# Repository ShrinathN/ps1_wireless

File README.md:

# Project to turn any original PS1 or PS2 controller wireless using an AVR and a NRF24L01/NRF24L01+ radio

## Hardware

* atmega8a
* NRF24L01+ / NRF24L01
* PS1 / PS2 controller
* 18650 + TP4056 (I'm using an 18650, but you can choose whatever you want)

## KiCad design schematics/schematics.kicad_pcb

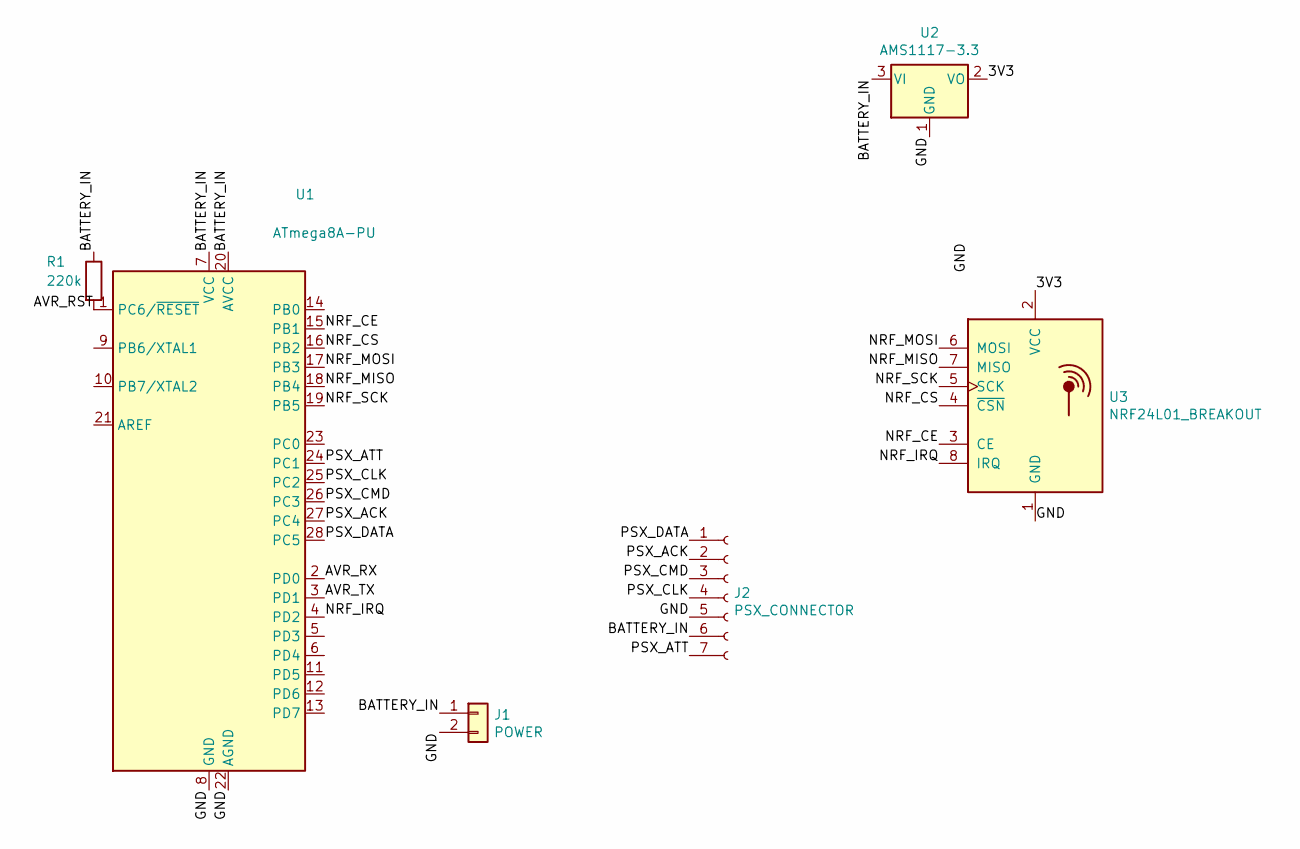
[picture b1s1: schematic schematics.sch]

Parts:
J1: POWER; PinHeader_1x02_P2.00mm_Vertical
J2: PSX_CONNECTOR; PinHeader_1x07_P2.54mm_Vertical
R1: 220k; R_Axial_DIN0204_L3.6mm_D1.6mm_P5.08mm_Horizontal
U1: ATmega8A-PU; DIP-28_W7.62mm
U2: AMS1117-3.3; SOT-223-3_TabPin2
U3: NRF24L01_BREAKOUT; nRF24L01_Breakout

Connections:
/3V3: U2.2 (VO), U3.2 (VCC)
/AVR_RST: R1.2, U1.1 (PC6/~RESET)
/AVR_RX: U1.2 (PD0)
/AVR_TX: U1.3 (PD1)
/BATTERY_IN: J1.1, J2.6, R1.1, U1.7 (VCC), U1.20 (AVCC), U2.3 (VI)
/GND: J1.2, J2.5, U1.8 (GND), U1.22 (AGND), U2.1 (GND), U3.1 (GND)
/NRF_CE: U1.15 (PB1), U3.3 (CE)
/NRF_CS: U1.16 (PB2), U3.4 (~CSN)
/NRF_IRQ: U1.4 (PD2), U3.8 (IRQ)
/NRF_MISO: U1.18 (PB4), U3.7 (MISO)
/NRF_MOSI: U1.17 (PB3), U3.6 (MOSI)
/NRF_SCK: U1.19 (PB5), U3.5 (SCK)
/PSX_ACK: J2.2, U1.27 (PC4)
/PSX_ATT: J2.7, U1.24 (PC1)
/PSX_CLK: J2.4, U1.25 (PC2)
/PSX_CMD: J2.3, U1.26 (PC3)
/PSX_DATA: J2.1, U1.28 (PC5)

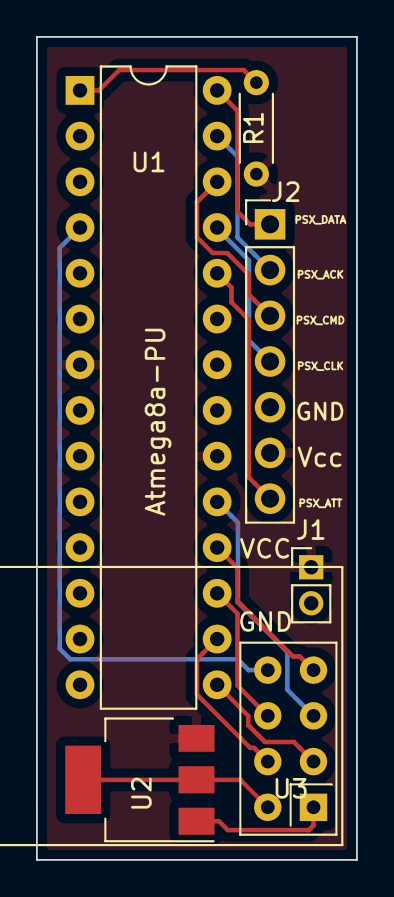
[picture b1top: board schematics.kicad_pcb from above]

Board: 2 copper layers, 17.8 x 45.7 mm, 6 parts (0 on the bottom side), 15 nets.

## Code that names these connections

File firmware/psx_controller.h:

#ifndef PSX_CONTROLLER_H
#define PSX_CONTROLLER_H
#include "main.h"

//constants
#define PSX_DELAY_CLK_US 10
#define PSX_ATT_DELAY_US 20
#define PSX_INTER_BYTE_DELAY_US 20

//pin definitions
#define PSX_ATT_DDR DDRC
#define PSX_ATT_PORT PORTC
#define PSX_ATT_BIT PC1

#define PSX_CLK_DDR DDRC
#define PSX_CLK_PORT PORTC
#define PSX_CLK_BIT PC2

#define PSX_CMD_DDR DDRC
#define PSX_CMD_PORT PORTC
#define PSX_CMD_BIT PC3

#define PSX_ACK_DDR DDRC
#define PSX_ACK_PORT PORTC
#define PSX_ACK_PIN PINC
#define PSX_ACK_BIT PC4

#define PSX_DATA_DDR DDRC
#define PSX_DATA_PORT PORTC
#define PSX_DATA_PIN PINC
#define PSX_DATA_BIT PC5

//MACROS
#define PSX_CLK_LOW PSX_CLK_PORT &= ~(1 << PSX_CLK_BIT)
#define PSX_CLK_HIGH PSX_CLK_PORT |= (1 << PSX_CLK_BIT)
#define PSX_ATT_LOW PSX_ATT_PORT &= ~(1 << PSX_ATT_BIT)
#define PSX_ATT_HIGH PSX_ATT_PORT |= (1 << PSX_ATT_BIT)
#define PSX_CMD_LOW PSX_CMD_PORT &= ~(1 << PSX_CMD_BIT)
#define PSX_CMD_HIGH PSX_CMD_PORT |= (1 << PSX_CMD_BIT)
#define PSX_READ_DATA ((PSX_DATA_PIN & (1 << PSX_DATA_BIT))?(1):(0))
#define PSX_WAIT_ACK while(PSX_ACK_PIN & (1 << PSX_ACK_BIT))
#define PSX_DELAY_US(x) _delay_us(x)

//different types of controllers
enum
{
	PSX_TYPE_DIGITAL = 0x41,
	PSX_TYPE_NEGCON = 0x23,
	PSX_TYPE_ANALOGUE_RED_LED = 0x73,
	PSX_TYPE_ANALOGUE_GREEN_LED = 0x53
};

//function declarations
void PSX_PinsInit();
void PSX_TransRecieveBlock(uint8_t * transmit_block, uint8_t * recieve_block, uint8_t length);

#endif

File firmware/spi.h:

#ifndef SPI_H
#define SPI_H
//header file includes
#include "main.h"

//pin definitions
#define SPI_DIRECTION_REGISTER DDRB
#define SPI_PORT PORTB
#define SPI_SCK_PIN PB5
#define SPI_MISO_PIN PB4
#define SPI_MOSI_PIN PB3
#define SPI_SS_PIN PB2

//macros
#define SPI_WAIT while(!(SPSR & (1 << SPIF))) //for waiting while the SPIF pin is not set in the SPSR register
#define SPI_SS_HIGH SPI_PORT |= (1 << SPI_SS_PIN)
#define SPI_SS_LOW SPI_PORT &= ~(1 << SPI_SS_PIN)

//function declarations
void SPI_Init();
void SPI_Transmit(uint8_t * data, uint8_t length);
void SPI_Receive(uint8_t * buffer, uint8_t length);
void SPI_TransReceive(uint8_t * data, uint8_t * buffer, uint8_t length);

#endif

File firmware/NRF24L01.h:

#ifndef NRF24L01_H
#define NRF24L01_H

#include "main.h"

//pin definitions
//CE pin
#define NRF_CE_DDR DDRB
#define NRF_CE_PORT PORTB
#define NRF_CE_BIT PB1
//IRQ pin
#define NRF_IRQ_DDR DDRD
#define NRF_IRQ_PORT PORTD
#define NRF_IRQ_PIN PIND
#define NRF_IRQ_BIT PD2

//macros
#define NRF_CSN_HIGH SPI_SS_HIGH
#define NRF_CSN_LOW SPI_SS_LOW
#define NRF_CE_HIGH NRF_CE_PORT |= (1 << NRF_CE_BIT)
#define NRF_CE_LOW NRF_CE_PORT &= ~(1 << NRF_CE_BIT)
#define NRF_IRQ_WAIT while((NRF_IRQ_PIN & (1 << NRF_IRQ_BIT)) != 0){}
#define NRF_DELAY_US(x) _delay_us(x)
#define NRF_DELAY_MS(x) _delay_ms(x)

//register names
enum
{
	REG_CONFIG = 0x0,
	REG_EN_AA,
	REG_EN_RXADDR,
	REG_SETUP_AW,
	REG_SETUP_RETR,
	REG_RF_CH,
	REG_RF_SETUP,
	REG_STATUS,
	REG_OBSERVE_TX,
	REG_RPD,
	REG_RX_ADDR_P0,
	REG_RX_ADDR_P1,
	REG_RX_ADDR_P2,
	REG_RX_ADDR_P3,
	REG_RX_ADDR_P4,
	REG_RX_ADDR_P5,
	REG_TX_ADDR,
	REG_RX_PW_P0,
	REG_RX_PW_P1,
	REG_RX_PW_P2,
	REG_RX_PW_P3,
	REG_RX_PW_P4,
	REG_RX_PW_P5,
	REG_FIFO_STATUS,
	REG_DYNPD = 0x1c,
	REG_FEATURE
};

//register 0x0
enum
{
	CONFIG_MASK_RX_DR_ON = 0x0,
	CONFIG_MASK_RX_DR_OFF = 0x40
};

enum
{
	CONFIG_MASK_TX_DS_ON = 0x0,
	CONFIG_MASK_TX_DS_OFF = 0x20
};

enum
{
	CONFIG_MASK_MAX_RT_ON = 0x0,
	CONFIG_MASK_MAX_RT_OFF = 0x10
};

enum
{
	CONFIG_EN_CRC_LOW = 0x0,
	CONFIG_EN_CRC_HIGH = 0x8
};

enum
{
	CONFIG_CRCO_ONE_BYTE = 0x0,
	CONFIG_CRCO_TWO_BYTE = 0x4
};

enum
{
	CONFIG_PWR_UP_DOWN = 0x0,
	CONFIG_PWR_UP_UP = 0x2
};

enum
{
	CONFIG_PRIM_RX_PTX = 0x0,
	CONFIG_PRIM_RX_PRX = 0x1
};

//register 0x1
enum
{
	EN_AA_ENAA_P5_ENABLE = 0x20,
	EN_AA_ENAA_P4_ENABLE = 0x10,
	EN_AA_ENAA_P3_ENABLE = 0x8,
	EN_AA_ENAA_P2_ENABLE = 0x4,
	EN_AA_ENAA_P1_ENABLE = 0x2,
	EN_AA_ENAA_P0_ENABLE = 0x1
};

//register 0x2
enum
{
	EN_RXADDR_ERX_P5_ENABLE = 0x20,
	EN_RXADDR_ERX_P4_ENABLE = 0x10,
	EN_RXADDR_ERX_P3_ENABLE = 0x8,
	EN_RXADDR_ERX_P2_ENABLE = 0x4,
	EN_RXADDR_ERX_P1_ENABLE = 0x2,
	EN_RXADDR_ERX_P0_ENABLE = 0x1
};

//register 0x3
enum
{
	SETUP_AW_AW_3_BYTES = 0x1,
	SETUP_AW_AW_4_BYTES = 0x2,
	SETUP_AW_AW_5_BYTES = 0x3
};

//register 0x4
enum
{
	SETUP_RETR_ARD_250US = 0x0,
	SETUP_RETR_ARD_500US = 0x10,
	SETUP_RETR_ARD_750US = 0x20,
	SETUP_RETR_ARD_1000US = 0x30,
	SETUP_RETR_ARD_1250US = 0x40,
	SETUP_RETR_ARD_1500US = 0x50,
	SETUP_RETR_ARD_1750US = 0x60,
	SETUP_RETR_ARD_2000US = 0x70,
	SETUP_RETR_ARD_2250US = 0x80,
	SETUP_RETR_ARD_2500US = 0x90,
	SETUP_RETR_ARD_2750US = 0xa0,
	SETUP_RETR_ARD_3000US = 0xb0,
	SETUP_RETR_ARD_3250US = 0xc0,
	SETUP_RETR_ARD_3500US = 0xd0,
	SETUP_RETR_ARD_3750US = 0xe0,
	SETUP_RETR_ARD_4000US = 0xf0
};

enum
{
	SETUP_RETR_ARC_0 = 0x0,
	SETUP_RETR_ARC_1 = 0x1,
	SETUP_RETR_ARC_2 = 0x2,
	SETUP_RETR_ARC_3 = 0x3,
	SETUP_RETR_ARC_4 = 0x4,
	SETUP_RETR_ARC_5 = 0x5,
	SETUP_RETR_ARC_6 = 0x6,
	SETUP_RETR_ARC_7 = 0x7,
	SETUP_RETR_ARC_8 = 0x8,
	SETUP_RETR_ARC_9 = 0x9,
	SETUP_RETR_ARC_10 = 0xa,
	SETUP_RETR_ARC_11 = 0xb,
	SETUP_RETR_ARC_12 = 0xc,
	SETUP_RETR_ARC_13 = 0xd,
	SETUP_RETR_ARC_14 = 0xe,
	SETUP_RETR_ARC_15 = 0xf
};

//register 0x6
enum
{
	RF_SETUP_CONT_WAVE = 0x80,
	RF_SETUP_PLL_LOCK = 0x10,
	RF_SETUP_DR_1MBPS = 0x0,
	RF_SETUP_DR_2MBPS = 0x8,
	RF_SETUP_DR_250KBPS = 0x20,
	RF_SETUP_RF_PWR_M18DBM = 0x0,
	RF_SETUP_RF_PWR_M12DBM = 0x2,
	RF_SETUP_RF_PWR_M6DBM = 0x4,
	RF_SETUP_RF_PWR_P0DBM = 0x6,
};

//register 0x7
enum
{
	STATUS_RX_DR_CLR = 0x40,
	STATUS_TX_DS_CLR = 0x20,
	STATUS_MAX_RT_CLR = 0x10
};

//function declarations
uint8_t NRF_ReadRegister(uint8_t regstr);
void NRF_WriteRegister(uint8_t regstr, uint8_t data);
void NRF_WriteTxFIFO(uint8_t *data, uint8_t length);
void NRF_ReadRxFIFO(uint8_t * ptr, uint8_t length);
void NRF_SetAddressTx(uint8_t * ptr, uint8_t length);
void NRF_SetMode(uint8_t mode);
void NRF_Init();
void NRF_Execute();
void NRF_FlushTxBuffer();

#endif

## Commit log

2020-02-12 Started firmware development
2020-02-12 Created schematics
2020-02-12 Schematics are done
2020-02-12 Working on the firmware
2020-02-12 Still writing firmware
2020-02-12 Working on the battery management now
2020-02-14 Added README.md
2020-02-15 What an absolute trainwreck. I'm too tired to d o anytinh
2020-02-15 Fixed the unfathomably small problem
2020-02-16 Have to make battery reporting work
2020-02-17 Turns out I didn't really need floating point math for this
2020-02-21 Gotta clean the NRF code
2020-02-21 Firmware complete
2020-02-21 Gotta fix IRQ problem
2020-02-23 AVR firmware works well. STM32 firmware added with USB HID, can be improved.
2020-02-24 Measuring the battery voltage using the internal bandgap voltage input (1.3V), removing the voltage divider
2020-02-25 Updated PCB.
